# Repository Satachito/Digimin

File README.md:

# Digimin

距離センサーで弾く、オープンな電子楽器。片手で音程、もう片手で音量を、2 つの ToF 距離センサーで読み取り、Raspberry Pi Pico 2 W で音を作って DAC から出す。設定はスマホのブラウザから変えられる。

An open electronic instrument played with two time-of-flight distance sensors — one hand for pitch, the other for volume. A Raspberry Pi Pico 2 W synthesizes the sound and sends it to an I2S DAC (PCM5102A); settings are edited from a phone browser over the board's own Wi-Fi.

## 特徴

- 音程: VL53L1X（約21回/秒）、音量: VL53L4CD（約100回/秒）。どちらのセンサーをどちらに付けても起動時に自動判別
- 波形（サイン・三角・ノコギリ）の混ぜ合わせ、ハーモニー、ビブラート、オーバードライブ、レスリー、コーラス、ディレイ、リバーブ
- 組み込みプリセット 10 種類、名前付きプリセット 7 つ、起動時の設定
- 本体が Wi-Fi アクセスポイント「Digimin-XXXX」になり、つなぐと操作画面が開く（日本語 / English）
- 音は PCM5102A（I2S DAC、96kHz、16bit）から出力。Wi-Fi はスイッチでオン / オフ

## 必要なもの

| 部品 | 数 |
|---|---|
| Raspberry Pi Pico 2 W | 1 |
| VL53L1X モジュール（音程） | 1 |
| VL53L4CD モジュール（音量） | 1 |
| PCM5102A DAC モジュール（紫色の基板、3.5mm ジャック付き） | 1 |
| トグルスイッチ ON-OFF-ON（センターオフ、3 ポジション） | 1 |

## ピン表

| 物理ピン | GP | つなぐ先 |
|---|---|---|
| 1 | GP0 | DAC LCK |
| 2 | GP1 | DAC BCK |
| 3 | GND | DAC SCK |
| 4 | GP2 | DAC DIN |
| 7 | GP5 | スイッチの片側（Wi-Fi オフ） |
| 8 | GND | スイッチの中央 |
| 12 | GP9 | スイッチの反対側（Wi-Fi パスワードなし） |
| 15 | GP11 | 音程センサー XSHUT |
| 16 | GP12 | 音程センサー SDA（I2C0） |
| 17 | GP13 | 音程センサー SCL（I2C0） |
| 18 | GND | 音程センサー GND |
| 23 | GND | 音量センサー GND |
| 24 | GP18 | 音量センサー SDA（I2C1） |
| 25 | GP19 | 音量センサー SCL（I2C1） |
| 26 | GP20 | 音量センサー XSHUT |
| 36 | 3V3(OUT) | センサー VIN ×2 |
| 38 | GND | DAC GND |
| 39 | VSYS | DAC VIN |

- センサーの GPIO1 は未接続。
- DAC モジュール裏のジャンパーは、H1（FLT）、H2（DEMP）、H4（FMT）を L、H3（XSMT）を H にする。H3 が L だとミュートされて音が出ない。
- 音は DAC モジュールの 3.5mm ジャック（または LROUT / ROUT / AGND の端子）から出す。左右は同じ音。

詳しい仕様は [theremin_pico2w/SPEC.md](theremin_pico2w/SPEC.md) を参照。

## ファームの書き込み

[arduino-pico](https://github.com/earlephilhower/arduino-pico)（Raspberry Pi Pico/RP2040/RP2350、6.2.0 で確認）と、Pololu の [VL53L1X](https://github.com/pololu/vl53l1x-arduino) ライブラリを使う。VL53L4CD のドライバはスケッチに含まれている。

```bash
arduino-cli core install rp2040:rp2040 --additional-urls https://github.com/earlephilhower/arduino-pico/releases/download/global/package_rp2040_index.json
arduino-cli lib install VL53L1X
arduino-cli compile --fqbn rp2040:rp2040:rpipico2w theremin_pico2w
arduino-cli upload --fqbn rp2040:rp2040:rpipico2w -p <ポート> theremin_pico2w
```

Arduino IDE なら、ボードに「Raspberry Pi Pico 2W」を選んで `theremin_pico2w/theremin_pico2w.ino` を開いて書き込む。

## 使い方

1. USB（モバイルバッテリーでも可）で電源を入れる
2. スイッチを中央にして Wi-Fi をオンにし、スマホで Wi-Fi「Digimin-XXXX」につなぐと操作画面が開く（開かなければ http://192.168.42.1/ ）
3. 音程センサーに手を近づけると高く、遠ざけると低くなる。音量センサーに手を近づけると大きくなる
4. スイッチで Wi-Fi を切り替える。中央でオン（パスワードを設定していればパスワードあり）、片側でオフ、反対側でパスワードなしでオン。パスワードを忘れたときは、パスワードなしの位置にすればつなげる（保存したパスワードは消えない）

## 旧版（PWM 版）

DAC を使わず、Pico の PWM 出力（約96kHz）と RC フィルタ 2 段で音を出す最初の版。Wi-Fi はつまみ（10kΩ B カーブ）で切り替える。センサーのピンも DAC 版と違う。部品と配線は [SPEC.md](theremin_pico2w/SPEC.md) の PWM 版の節を参照。

- ファームは同じファイル。`-DDIGIMIN_DAC=0` を付けてビルドする（Arduino IDE なら、スケッチの `#define DIGIMIN_DAC 1` を `0` に書き換える）

```bash
arduino-cli compile --fqbn rp2040:rp2040:rpipico2w --build-property "compiler.cpp.extra_flags=-DDIGIMIN_DAC=0" theremin_pico2w
```

- Wi-Fi の電波を出している間は、3.3V の揺れが PWM の振幅に出て、小さなノイズが乗る。演奏するときはつまみを絞り切って Wi-Fi を切る
- RC フィルタ・ジャック・つまみ用の基板（KiCad、JLCPCB 向けの製造データ付き）は [theremin_pico2w/kicad/](theremin_pico2w/kicad/)

## ライセンス

MIT License（[LICENSE](LICENSE)）

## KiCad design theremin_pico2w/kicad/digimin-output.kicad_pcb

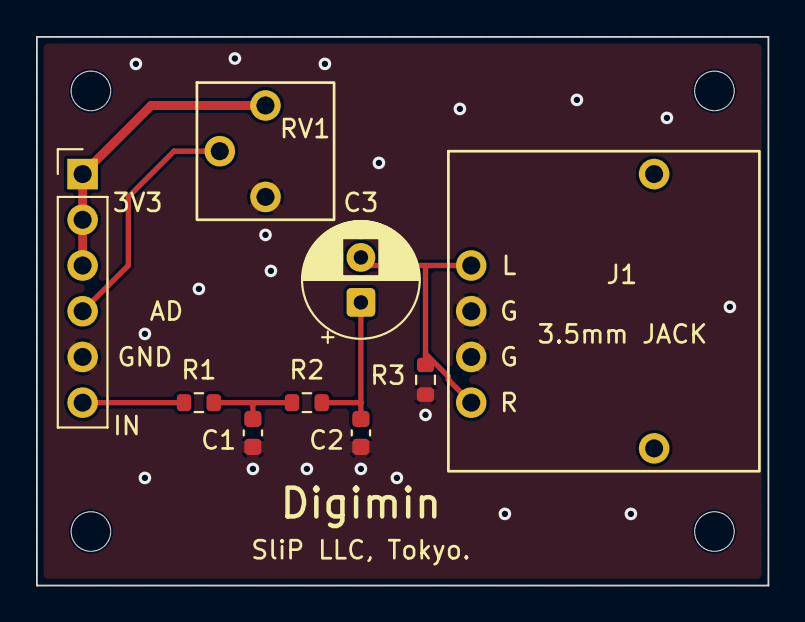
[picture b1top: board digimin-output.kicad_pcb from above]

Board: 2 copper layers, 40.6 x 30.5 mm, 13 parts (0 on the bottom side), 7 nets.

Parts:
C1, C2: 10n; C_0603_1608Metric
C3: 10u; CP_Radial_D6.3mm_P2.50mm
H1, H2, H3, H4: M2; MountingHole_2.2mm_M2
J1: 3.5mm Jack (L G G R); Jack_7x7
J2: IN AD GND 3V3; PinHeader_1x06_P2.54mm_Vertical
R1, R2: 1k; R_0603_1608Metric
R3: 3.3k; R_0603_1608Metric
RV1: 10k B; Pot_3x3

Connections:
+3V3: J2.1, J2.2, J2.3, RV1.1
/KNOB: J2.4, RV1.2
/N1: C1.1, R1.2, R2.1
/N2: C2.1, C3.1, R2.2
/OUT: C3.2, J1.1, J1.4, R3.1
/PWM: J2.6, R1.1
GND: C1.2, C2.2, J1.2, J1.3, J2.5, R3.2, RV1.3
